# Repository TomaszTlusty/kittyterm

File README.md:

# KittyTerm

KittyTerm is a tiny motion-controlled digital pet: basically a desktop Tamagotchi with a 3-button control scheme and motion sensing. You can interact with it both by physically moving the board and by using the onboard push buttons.

## What it is

KittyTerm is designed to sit on your desk, show its personality on a small OLED display, and react to how you handle it. Tilting, shaking, and checking in on your pet are all part of the experience.

The board includes a Seeed XIAO ESP32-C3 microcontroller, an SSD1306 OLED display, an MPU6050 motion sensor, a DHT11 environmental sensor, and three push buttons in a compact, USB-powered PCB design built around beginner-friendly through-hole soldering.

## Why?

This project was created for the week 1 beginner tutorial for [halflife](https://halflife.hackclub.com/)!

## Project status

The PCB design, renders, and starter firmware are included here. The program features an animated pet with a tilt- and button-controlled radial menu, live environmental stats, persistent memory, and shake reactions.

## Software

[`Firmware/`](Firmware/) contains a single-file, non-blocking (`millis()`-based) sketch for the **Seeed XIAO ESP32-C3**, compatible with both Arduino IDE and PlatformIO.

### Key Firmware Features

- **Three Screen Views (`View` State Machine)**:
  - **`PET_VIEW`**: Renders a custom 32x32 1-bit `PROGMEM` sprite on a 128x64 SSD1306 OLED (`0x3C`). The pet wanders across the screen and plays procedural animations for jumping, running laps, sleeping (with floating `z`s), and emitting hearts.
  - **`MENU_VIEW`**: A 4-sector radial menu (`NAP`, `PLAY`, `FEED`, `PET`). Opening the menu records the board's current tilt angle as a zero-point calibration, turning the MPU6050 (`0x68`) into a smoothed air-mouse cursor with a configurable center deadzone.
  - **`STATS_VIEW`**: Displays 0–100 stat bars for `JOY`, `ENERGY`, and `FULL`, alongside live ambient temperature and humidity readings polled from the DHT11 sensor.
- **Hybrid 3-Button & Motion Controls** (with 30 ms software debouncing):
  - **Button 1 (`GPIO 4` / `D2`)**: Opens the radial menu, confirms the highlighted action, or cancels if pressed while in the center deadzone.
  - **Button 2 (`GPIO 5` / `D3`)**: Toggles between the main pet screen and the stats screen.
  - **Button 3 (`GPIO 2` / `D0`)**: Cycles through the 4 radial menu options when the menu is open (allowing full navigation even without tilting), triggers a quick `PET` reaction on the main screen, or exits the stats screen.
  - **Shake Detection**: Continuously computes the 3D acceleration vector magnitude from the MPU6050. Shaking the board past the gravity threshold wakes the pet from naps, triggers a wiggle animation, and boosts `JOY`.
- **Persistent Flash Storage (`Preferences.h`)**:
  - Automatically saves `joy`, `energy`, and `fullness` values to the ESP32-C3's Non-Volatile Storage (NVS) after every action or shake so your pet's progress is kept across power cycles.
- **Beginner-Friendly Customization**:
  - All GPIO pin mappings, I2C addresses, starting stats, menu reactions, MPU6050 axis orientation (`SWAP_MPU_AXES`), and sprite bitmaps are grouped in the `BEGINNER SETTINGS` section at the top of the file.

### Required Libraries

- `Adafruit GFX Library`
- `Adafruit SSD1306`
- `Adafruit MPU6050` (with `Adafruit Unified Sensor` and `Adafruit BusIO`)
- `DHT sensor library`

## Repository contents

- `PCB/` - KiCad source files and fabrication exports
- `Images/` - front and back PCB renders
- `Week 1 Guide.md` - project guide material
- `Firmware/` - Arduino IDE / PlatformIO starter sketch

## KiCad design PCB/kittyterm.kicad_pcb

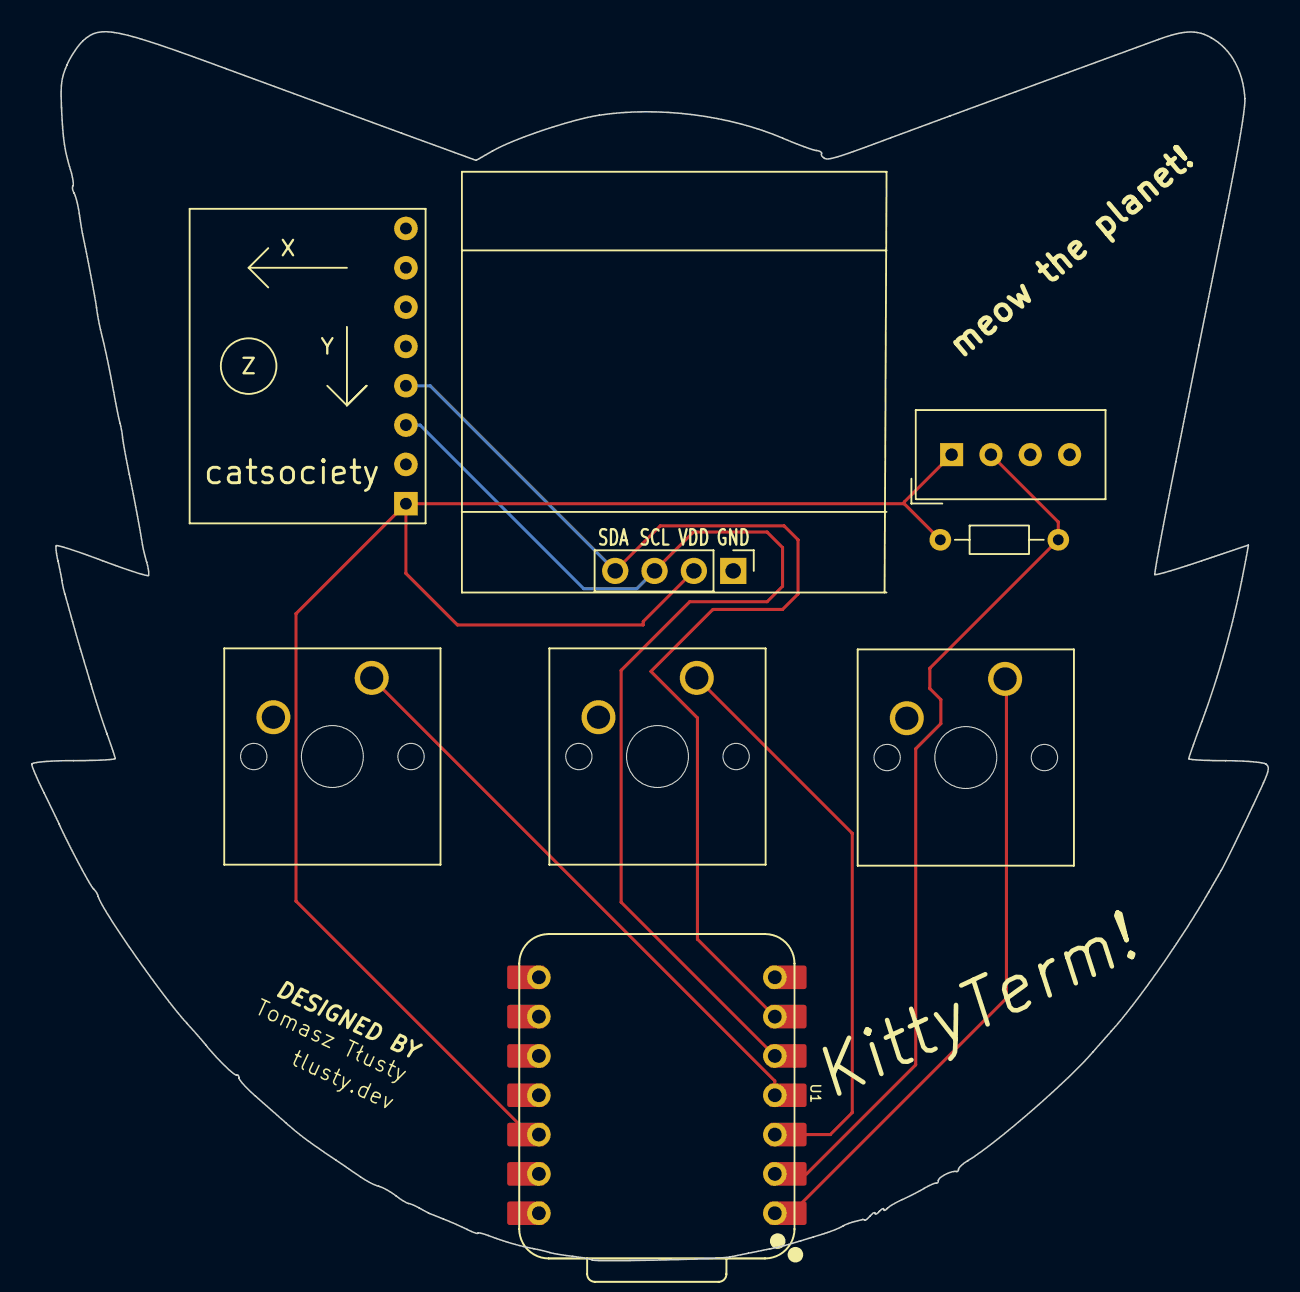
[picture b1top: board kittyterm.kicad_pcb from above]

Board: 2 copper layers, 79.9 x 79.4 mm, 8 parts (0 on the bottom side), 8 nets.

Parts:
J1: Conn_01x04; Display_128x64_096_I2C
J2: Conn_01x08; MPU6050_Module
R1: R; R_Axial_DIN0204_L3.6mm_D1.6mm_P7.62mm_Horizontal
SW1, SW2, SW3: SW_Push; SW_Cherry_MX_1.00u_PCB
U1: XIAO-ESP32-C3-DIP; XIAO-ESP32-C6-DIP
U2: DHT11; Aosong_DHT11_5.5x12.0_P2.54mm

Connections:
+3.3V: J1.2, J2.1, R1.1, U1.12 (3V3_OUT), U2.1 (VDD)
/DHT11 DATA: R1.2, U1.2 (D1), U2.2 (DATA)
/GPIO1: SW3.1, U1.1 (D0)
/GPIO2: SW1.1, U1.3 (D2)
/GPIO3: SW2.1, U1.4 (D3)
/SCL: J1.3, J2.3, U1.5 (D4)
/SDA: J1.4, J2.4, U1.6 (D5)
GND: J1.1, J2.2, SW1.2, SW2.2, SW3.2, U1.13 (GND), U2.4 (GND)
